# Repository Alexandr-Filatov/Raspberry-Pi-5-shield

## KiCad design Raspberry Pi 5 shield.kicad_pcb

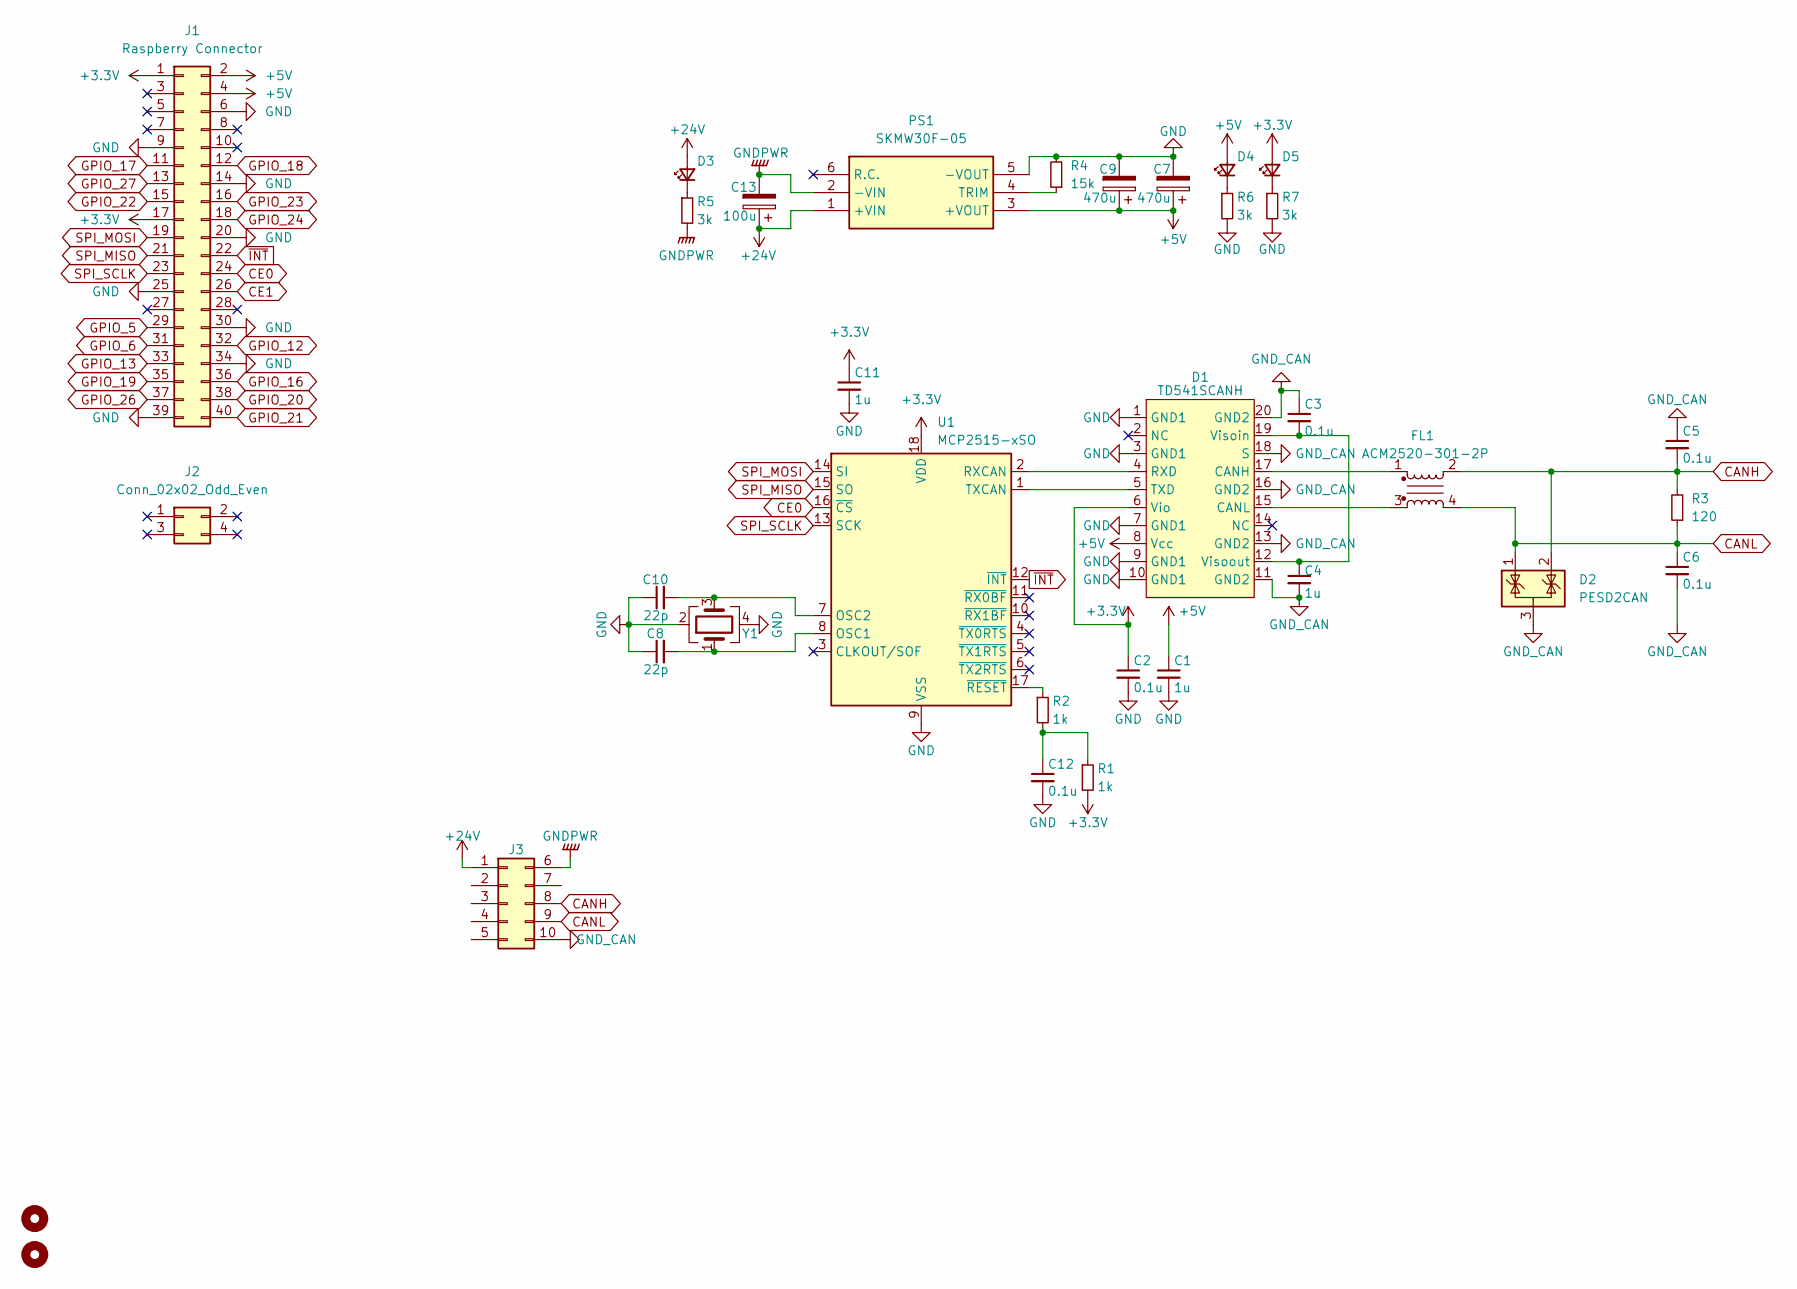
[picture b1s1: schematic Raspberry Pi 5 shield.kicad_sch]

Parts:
C1, C4, C11: 1u; C_0805_2012Metric_Pad1.18x1.45mm_HandSolder
C2, C3, C5, C6, C12: 0.1u; C_0805_2012Metric_Pad1.18x1.45mm_HandSolder
C7, C9: 470u; CP_Elec_10x10
C8, C10: 22p; C_0805_2012Metric_Pad1.18x1.45mm_HandSolder
C13: 100u; CP_Elec_10x10
D1: TD541SCANH; DFN-20
D2: PESD2CAN; SOT-23
D3: PWR; LED_0805_2012Metric_Pad1.15x1.40mm_HandSolder
D4, D5: LED_Small; LED_0805_2012Metric_Pad1.15x1.40mm_HandSolder
FL1: ACM2520-301-2P; ACM25201022PT002
H5, H6: MountingHole; MountingHole_3.2mm_M3
J1: Raspberry Connector; PinSocket_2x20_P2.54mm_Vertical
J2: Conn_02x02_Odd_Even; PinSocket_2x02_P2.54mm_Vertical
J3: DS1073-01-2x5-MVT6; MIni-Fit_02x05_Vertical
PS1: SKMW30F-05; SKMW30G12; Manufacturer_Part_Number SKMW30F-05; Mouser Part Number 709-SKMW30F-05
R1, R2: 1k; R_0805_2012Metric_Pad1.20x1.40mm_HandSolder
R3: 120; R_0805_2012Metric_Pad1.20x1.40mm_HandSolder
R4: 15k; R_0805_2012Metric_Pad1.20x1.40mm_HandSolder
R5, R6, R7: 3k; R_0805_2012Metric_Pad1.20x1.40mm_HandSolder
U1: MCP2515-xSO; SOIC-18W_7.5x11.6mm_P1.27mm
Y1: X322516MOB4SI

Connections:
+3.3V: C2.1, C11.1, D1.6 (Vio), D5.2 (A), J1.1, J1.17, R1.2, U1.18 (VDD)
+5V: C1.1, C7.1, C9.1, D1.8 (Vcc), D4.2 (A), J1.2, J1.4, PS1.3 (+VOUT)
+24V: C13.1, D3.2 (A), J3.1, PS1.1 (+VIN)
CANH: C5.2, D2.2 (K), FL1.2, J3.8, R3.2
CANL: C6.1, D2.1 (K), FL1.4, J3.9, R3.1
CE0: J1.24, U1.16 (~CS)
CE1: J1.26
GND: C1.2, C2.2, C7.2, C8.1, C9.2, C10.1, C11.2, C12.2, D1.1 (GND1), D1.3 (GND1), D1.7 (GND1), D1.9 (GND1), D1.10 (GND1), J1.6, J1.9, J1.14, J1.20, J1.25, J1.30, J1.34, J1.39, PS1.5 (-VOUT), R4.2, R6.2, R7.2, U1.9 (VSS), Y1.2, Y1.4
GNDPWR: C13.2, J3.6, PS1.2 (-VIN), R5.2
GND_CAN: C3.1, C4.2, C5.1, C6.2, D1.11 (GND2), D1.13 (GND2), D1.16 (GND2), D1.18 (S), D1.20 (GND2), D2.3 (A), J3.10
GPIO_5: J1.29
GPIO_6: J1.31
GPIO_12: J1.32
GPIO_13: J1.33
GPIO_16: J1.36
GPIO_17: J1.11
GPIO_18: J1.12
GPIO_19: J1.35
GPIO_20: J1.38
GPIO_21: J1.40
GPIO_22: J1.15
GPIO_23: J1.16
GPIO_24: J1.18
GPIO_26: J1.37
GPIO_27: J1.13
unnamed: C12.1, R1.1, R2.2
unnamed: D1.17 (CANH), FL1.1
unnamed: D1.15 (CANL), FL1.3
unnamed: D1.4 (RXD), U1.2 (RXCAN)
unnamed: D1.5 (TXD), U1.1 (TXCAN)
unnamed: C3.2, C4.1, D1.12 (Visoout), D1.19 (Visoin)
unnamed: D3.1 (K), R5.1
unnamed: D4.1 (K), R6.1
unnamed: D5.1 (K), R7.1
unnamed: PS1.4 (TRIM), R4.1
unnamed: C8.2, U1.8 (OSC1), Y1.1
unnamed: C10.2, U1.7 (OSC2), Y1.3
unnamed: R2.1, U1.17 (~RESET)
SPI_MISO: J1.21, U1.15 (SO)
SPI_MOSI: J1.19, U1.14 (SI)
SPI_SCLK: J1.23, U1.13 (SCK)
~INT: J1.22, U1.12 (~INT)

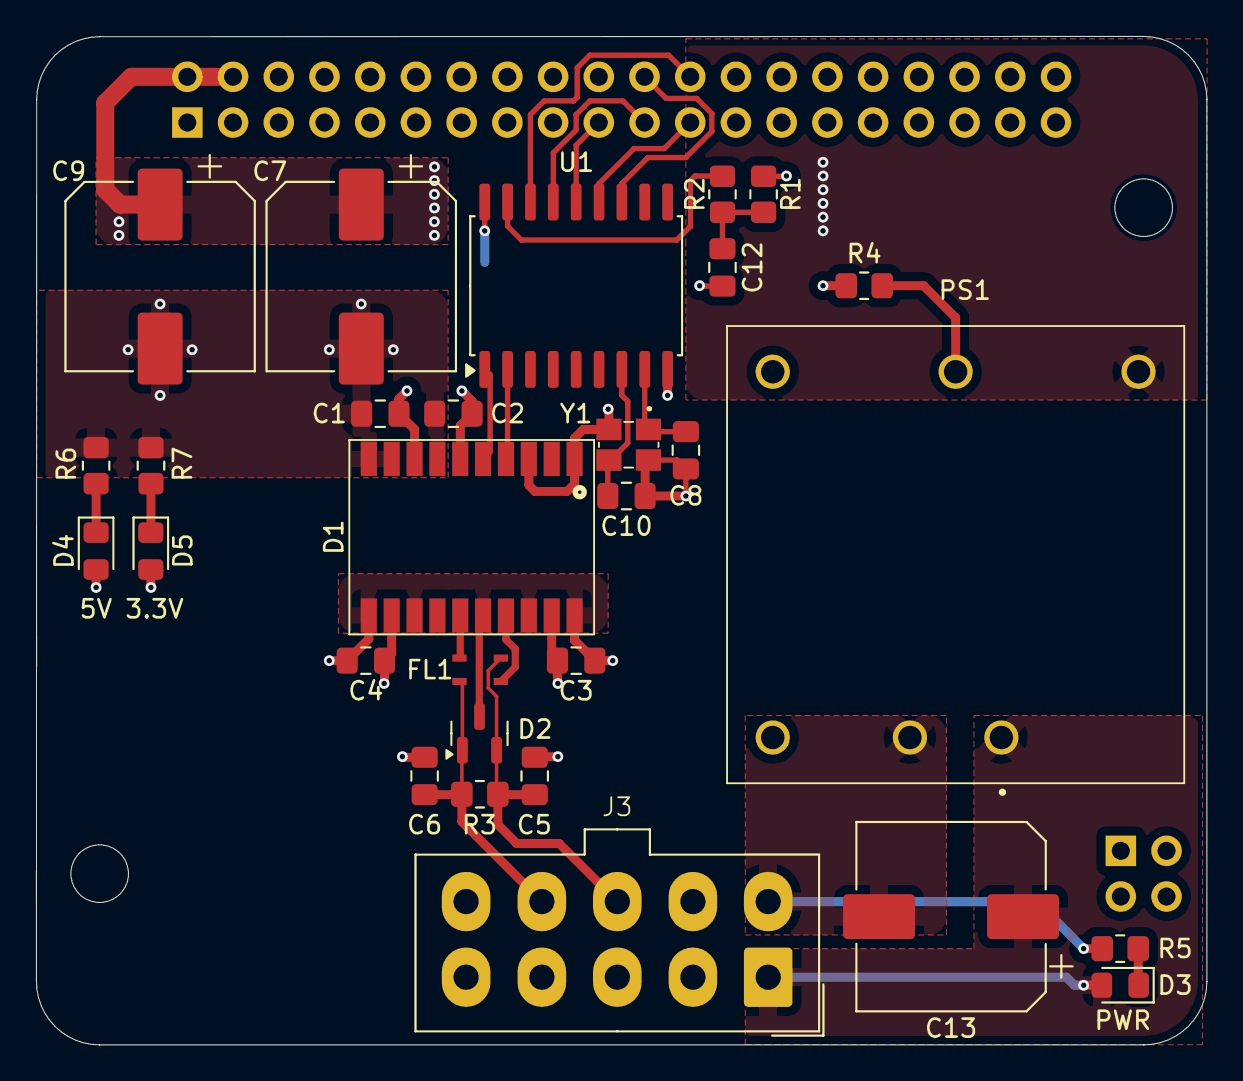
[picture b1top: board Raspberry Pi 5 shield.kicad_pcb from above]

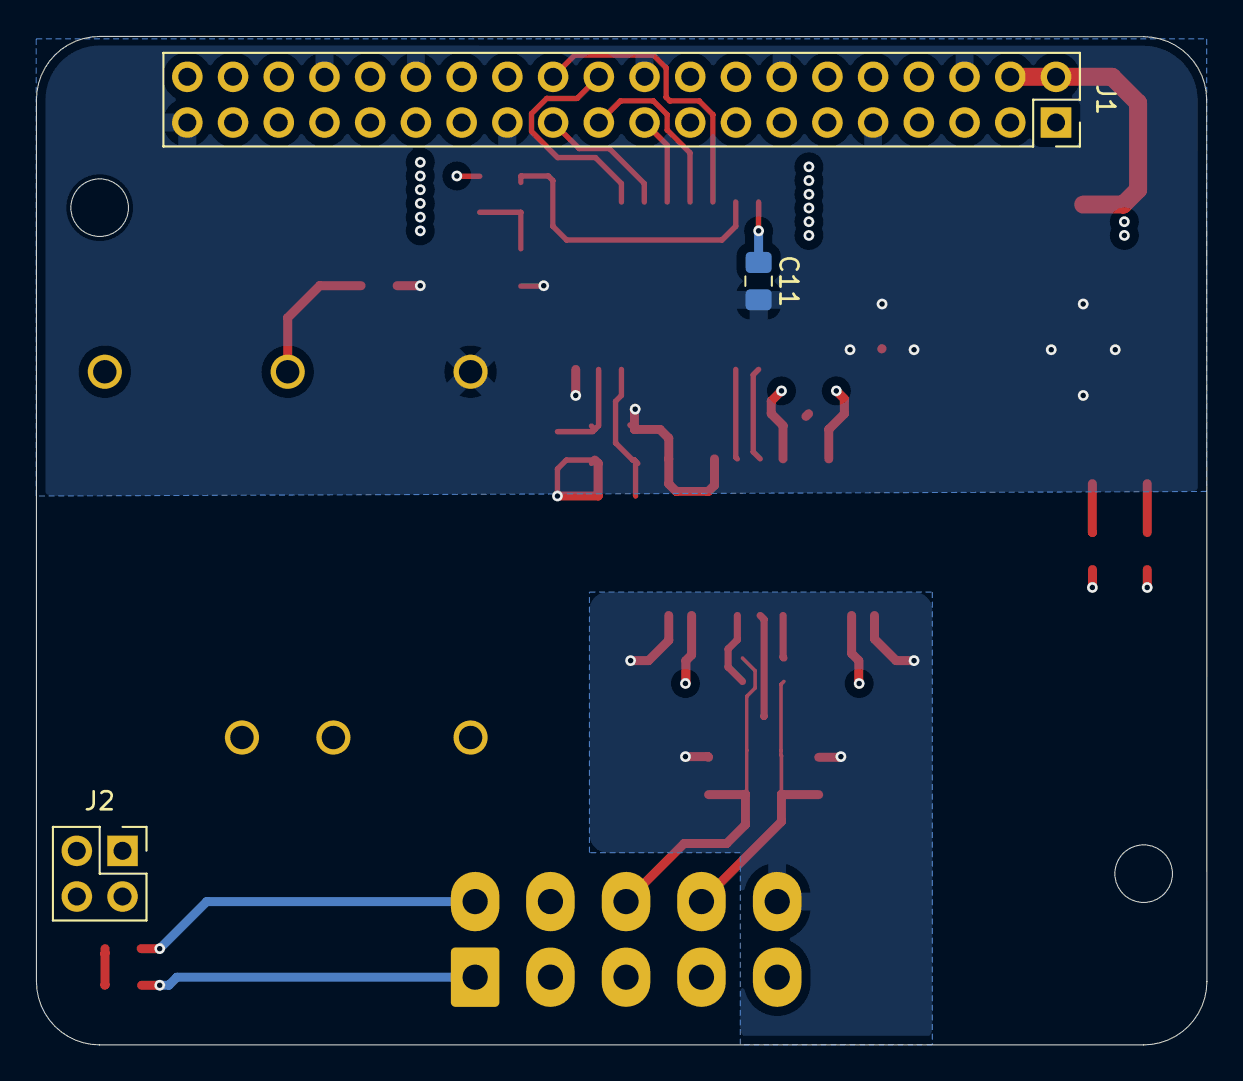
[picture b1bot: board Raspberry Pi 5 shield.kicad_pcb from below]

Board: 4 copper layers, 65.0 x 56.0 mm, 34 parts (3 on the bottom side), 26 nets.

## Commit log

2024-09-04 Zero commit
2024-09-05 Добавил подстроечный резистор к источнику питания
2024-09-12 Добавил конденсаторы по выходу
2024-09-16 Добавил индикацию
2024-09-16 Добавил BOM
2024-09-16 Исправил косяки в схеме
2024-09-16 Добавил гербера
